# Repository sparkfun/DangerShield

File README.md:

Danger Shield
=============

[  
*Danger Shield (DEV-10570)*](https://www.sparkfun.com/products/10570)

This is the layout and example code for the Danger Shield product by SparkFun Electronics. It demonstrates each feature of the shield. Move one of the sliders to get a different sound out of the buzzer. Move another slider to change the digit being displayed on the seven segment display. Move the last slider to change the brightness of one of the two status LEDs. Press one of the large buttons to toggle on/off the status LED. Cover the light sensor to 'scare' the unit.

The idea of a Danger Shield was originally created by Zach Hoeken ([http://www.zachhoeken.com/](http://www.zachhoeken.com/))

Repository Contents
-------------------
* **/Firmware** - Example Arduino Sketch
* **/Hardware** - All Eagle design files (.brd, .sch)

Product History
---------------

[DEV-09597](https://www.sparkfun.com/products/9597) - *retired*  
The original version of the Danger Shield which has since been retired.

[DEV-10115](https://www.sparkfun.com/products/10115) - *retired*  
Second version which introduced a knock sensor and a new temperature sensor. Has since been retired.

**[DEV-10570](https://www.sparkfun.com/products/10570) - current version**  
This newest version introduces a capacitive touch sensor. All code in this repository will work best with this version.

License Information
-------------------

The hardware is released under [Creative Commons Share-alike 3.0](http://creativecommons.org/licenses/by-sa/3.0/).  
The code is public domain but you buy me a beer if you use this and we meet someday ([Beerware license](http://en.wikipedia.org/wiki/Beerware)).

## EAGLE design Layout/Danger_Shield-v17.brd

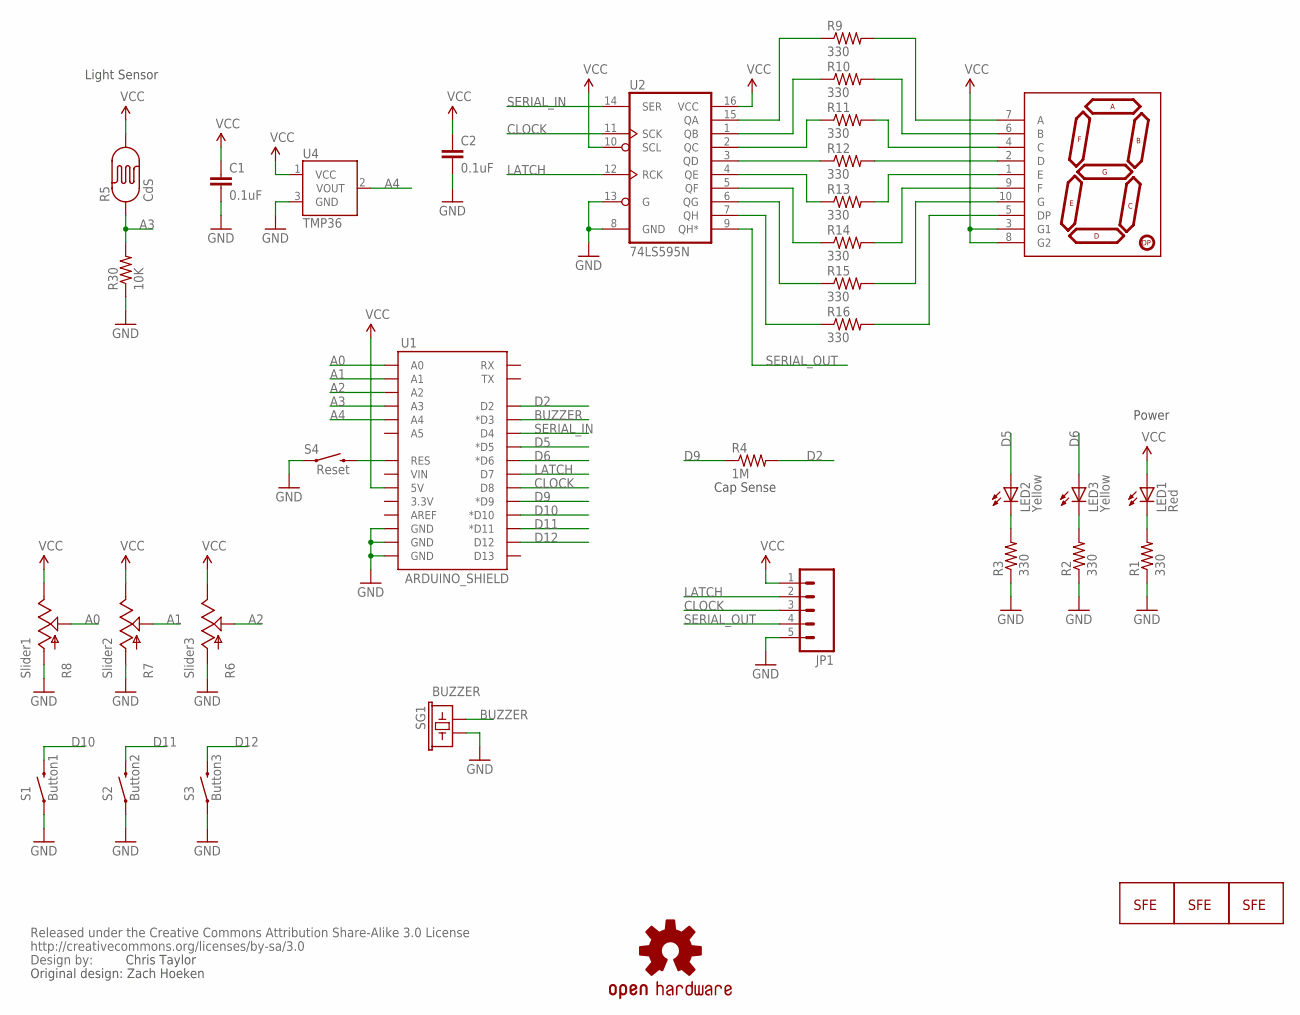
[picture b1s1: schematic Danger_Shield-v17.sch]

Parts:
C1, C2: 0.1uF; CAP-PTH-SMALL2
JP1: M05PTH; 1X05
JP2, JP3: LOGO-SFENEW; SFE-NEW-WEBLOGO
JP5: LOGO-SFESK; SFE-LOGO-FLAME
LED1: Red; LED5MM
LED2, LED3: Yellow; LED5MM
R1, R2, R3, R9, R10, R11, R12, R13, R14, R15, R16: 330; AXIAL-0.3
R4: 1M; AXIAL-0.3
R5: CdS; PHOTOCELL
R6: Slider3; SLIDER
R7: Slider2; SLIDER
R8: Slider1; SLIDER
R30: 10K; AXIAL-0.3
S1: Button1; TACTILE-PTH-12MM
S2: Button2; TACTILE-PTH-12MM
S3: Button3; TACTILE-PTH-12MM
S4: Reset; TACTILE-PTH
SG1: BUZZER; BUZZER-12MM
U1: ARDUINO_SHIELD; DUEMILANOVE_VIAS
U2: 74LS595N; DIL16
U4: TMP36; TO-92
U6: 7-SEGMENT-DISPLAY-1"-RED; 7-SEGMENT-1"PTH
U$1: CREATIVE_COMMONS
U$2: OSHW-LOGOM; OSHW-LOGO-M

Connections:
A0: R8.2A (S), U1.A0
A1: R7.2A (S), U1.A1
A2: R6.2A (S), U1.A2
A3: R5.1, R30.P$2 (2), U1.A3
A4: U1.A4, U4.2 (VOUT)
BUZZER: SG1.+ (1), U1.D3 (*D3)
CLOCK: JP1.3, U1.D8, U2.11 (SCK)
D2: R4.P$2 (2), U1.D2
D5: LED2.A, U1.D5 (*D5)
D6: LED3.A, U1.D6 (*D6)
D9: R4.P$1 (1), U1.D9 (*D9)
D10: S1.3 (2), U1.D10 (*D10)
D11: S2.3 (2), U1.D11 (*D11)
D12: S3.3 (2), U1.D12
GND: C1.2, C2.2, JP1.5, R1.P$1 (1), R2.P$1 (1), R3.P$1 (1), R6.3 (A), R7.3 (A), R8.3 (A), R30.P$1 (1), S1.1, S2.1, S3.1, S4.1, SG1.- (2), U1.GND@0 (GND), U1.GND@1 (GND), U1.GND@2 (GND), U2.8 (GND), U2.13 (G), U4.3 (GND)
LATCH: JP1.2, U1.D7, U2.12 (RCK)
unnamed: S4.3 (2), U1.RES
unnamed: R9.P$1 (1), U2.15 (QA)
unnamed: LED1.K (C), R1.P$2 (2)
unnamed: R10.P$1 (1), U2.1 (QB)
unnamed: R11.P$1 (1), U2.2 (QC)
unnamed: R12.P$1 (1), U2.3 (QD)
unnamed: R13.P$1 (1), U2.4 (QE)
unnamed: R14.P$1 (1), U2.5 (QF)
unnamed: R15.P$1 (1), U2.6 (QG)
unnamed: R16.P$1 (1), U2.7 (QH)
unnamed: R9.P$2 (2), U6.7 (A)
unnamed: R10.P$2 (2), U6.6 (B)
unnamed: R11.P$2 (2), U6.4 (C)
unnamed: R12.P$2 (2), U6.2 (D)
unnamed: R13.P$2 (2), U6.1 (E)
unnamed: R14.P$2 (2), U6.9 (F)
unnamed: R15.P$2 (2), U6.10 (G)
unnamed: R16.P$2 (2), U6.5 (DP)
unnamed: LED3.K (C), R2.P$2 (2)
unnamed: LED2.K (C), R3.P$2 (2)
SERIAL_IN: U1.D4, U2.14 (SER)
SERIAL_OUT: JP1.4, U2.9 (QH*)
VCC: C1.1, C2.1, JP1.1, LED1.A, R5.2, R6.1 (E), R7.1 (E), R8.1 (E), U1.5V, U2.10 (SCL), U2.16 (VCC), U4.1 (VCC), U6.3 (G1), U6.8 (G2)

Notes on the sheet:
Power
Light Sensor
Cap Sense
Chris Taylor
Original design: Zach Hoeken

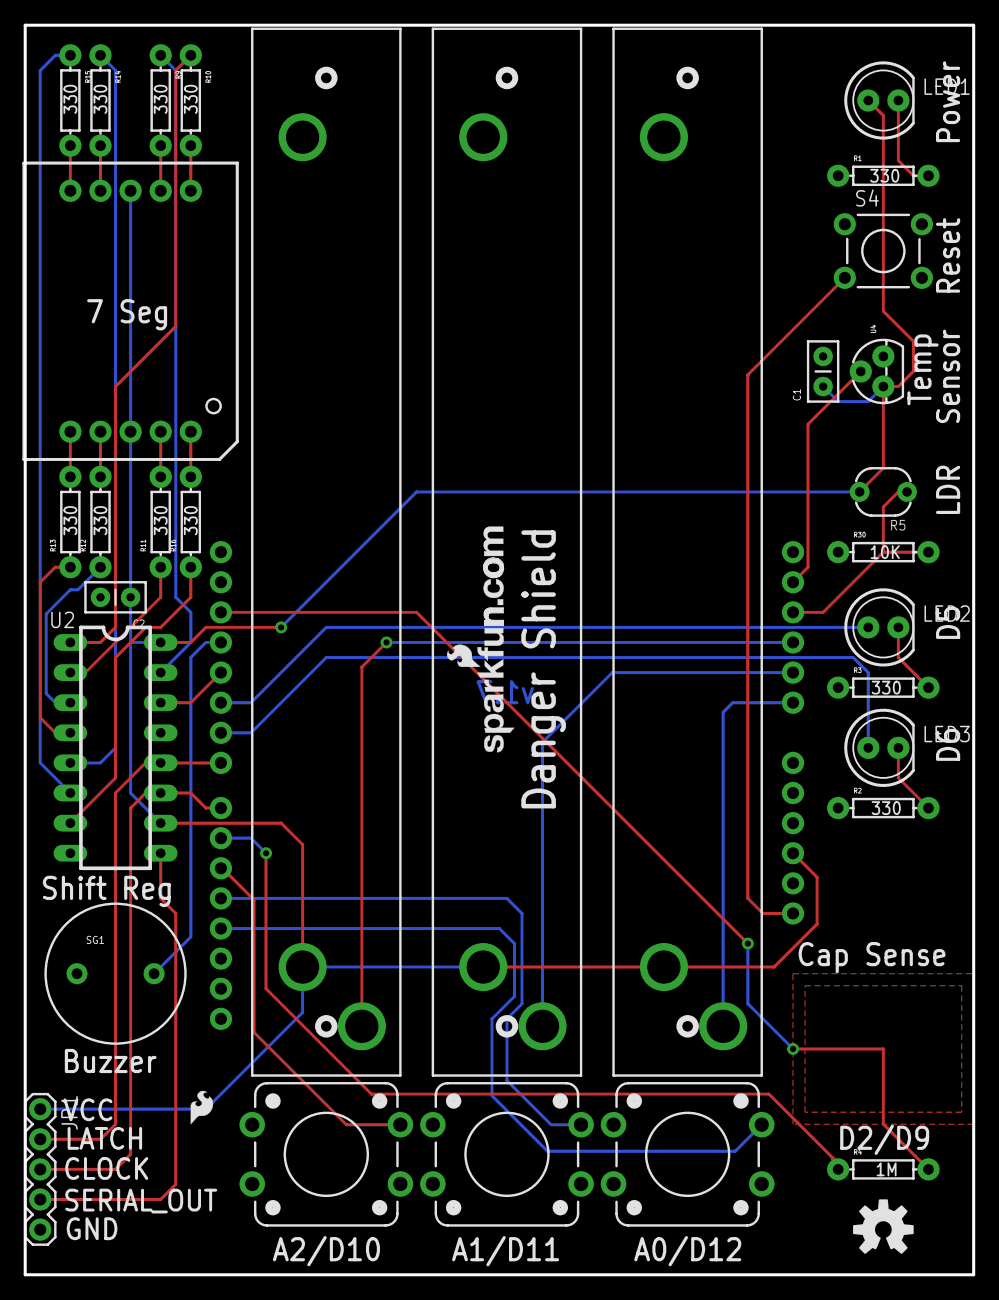
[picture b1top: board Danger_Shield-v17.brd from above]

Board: 2 copper layers, 80.0 x 105.4 mm, 37 parts (1 on the bottom side), 39 nets.

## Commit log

2012-10-22 Original commit, but new version of example code
    New example code does not require terminal or button pressing to cycle
    through features.
2012-10-22 v1.7 changes temp sensor to TMP36. Add 2 caps.
    Removed 10k on temp sensor. Changed to TMP36. Added 2 x 0.1uF caps for
    decoupling on shift register and temp sensor.
2012-10-22 Cosmetic updates to schematic.
2012-10-22 Added CC license to schematic and PCB.
2012-10-22 Added version # 1.7 to PCB.
2012-10-28 Update to gitignore. Added OSHW logo. Fixed overlapping resistors.
    Cleaned up the example code slightly as well. Trying to fit into
    SparkFun coding standards.
2012-10-28 Removing incremental backup files. These are now ignored in gitignore.
2012-10-29 Adding dimensional and BOM.
2012-10-29 Small change to example code.
2013-01-10 Added support for v1.7 PCB.
    Used sprintfs to print the the readings in a pretty way. Added
    CapacitiveSense based on latest Arduino library (it's no longer
    capsense, instead it's CapacitiveSense).
2013-03-07 porting README to markdown, adding images, organizing, etc.
2013-09-03 Fixing repo structure, and updating README
2015-01-14 Fixed map() functions
    functions now map fro 0 to 1023 instead of 0 to 1020
2025-06-27 Update README.md
    Updating link

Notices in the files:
parts and their libraries:
SparkFun-Sensors: Licensing: CC v3.0 Share-Alike You are welcome to use this library for commercial purposes.
SparkFun-Aesthetics: Released under the Creative Commons Attribution Share-Alike 3.0 License
SparkFun-Aesthetics: Creative Commons License summary
